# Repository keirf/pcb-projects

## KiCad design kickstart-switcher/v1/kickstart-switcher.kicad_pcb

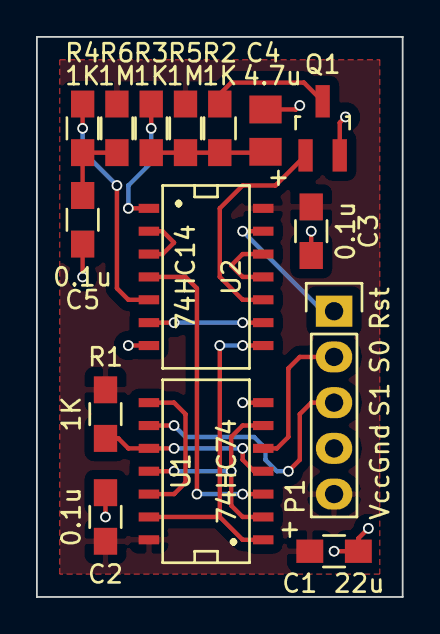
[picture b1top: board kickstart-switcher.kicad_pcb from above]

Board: 2 copper layers, 20.3 x 31.1 mm, 15 parts (0 on the bottom side), 19 nets.

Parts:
C1: 22u; R_0805_HandSoldering
C2, C3, C5: 0.1u; R_0805_HandSoldering
C4: 4.7u; TantalC_SizeR_EIA-2012
P1: CONN_01X05; Pin_Header_Straight_1x05
Q1: Q_NMOS; SOT-23_Handsoldering
R1, R2, R3, R4: 1K; R_0805_HandSoldering
R5, R6: 1M; R_0805_HandSoldering
U1: 74HC74; SOIC-14_N
U2: 74HC14; SOIC-14_N

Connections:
+5V: C1.1, C2.1, C3.1, P1.5, R1.1, R5.1, R6.1, U1.14, U2.14
//RESET: P1.1, U2.13
/CLR: U1.1, U1.13, U2.8
/SEL0: P1.2, U1.5
/SEL1: P1.3, U1.9
GND: C1.2, C2.2, C3.2, C4.2, C5.2, P1.4, Q1.2, U1.7, U2.7
unnamed: C4.1, R2.1, R3.2, R5.2
unnamed: C5.1, R4.2, R6.2
unnamed: Q1.1, U2.10
unnamed: Q1.3, R2.2
unnamed: R1.2, U1.4, U1.10
unnamed: R3.1, U2.1
unnamed: R4.1, U2.5
unnamed: U1.3, U2.4
unnamed: U1.2, U1.6, U1.11
unnamed: U1.8, U1.12
unnamed: U2.2, U2.3
unnamed: U2.6, U2.9
unnamed: U2.11, U2.12

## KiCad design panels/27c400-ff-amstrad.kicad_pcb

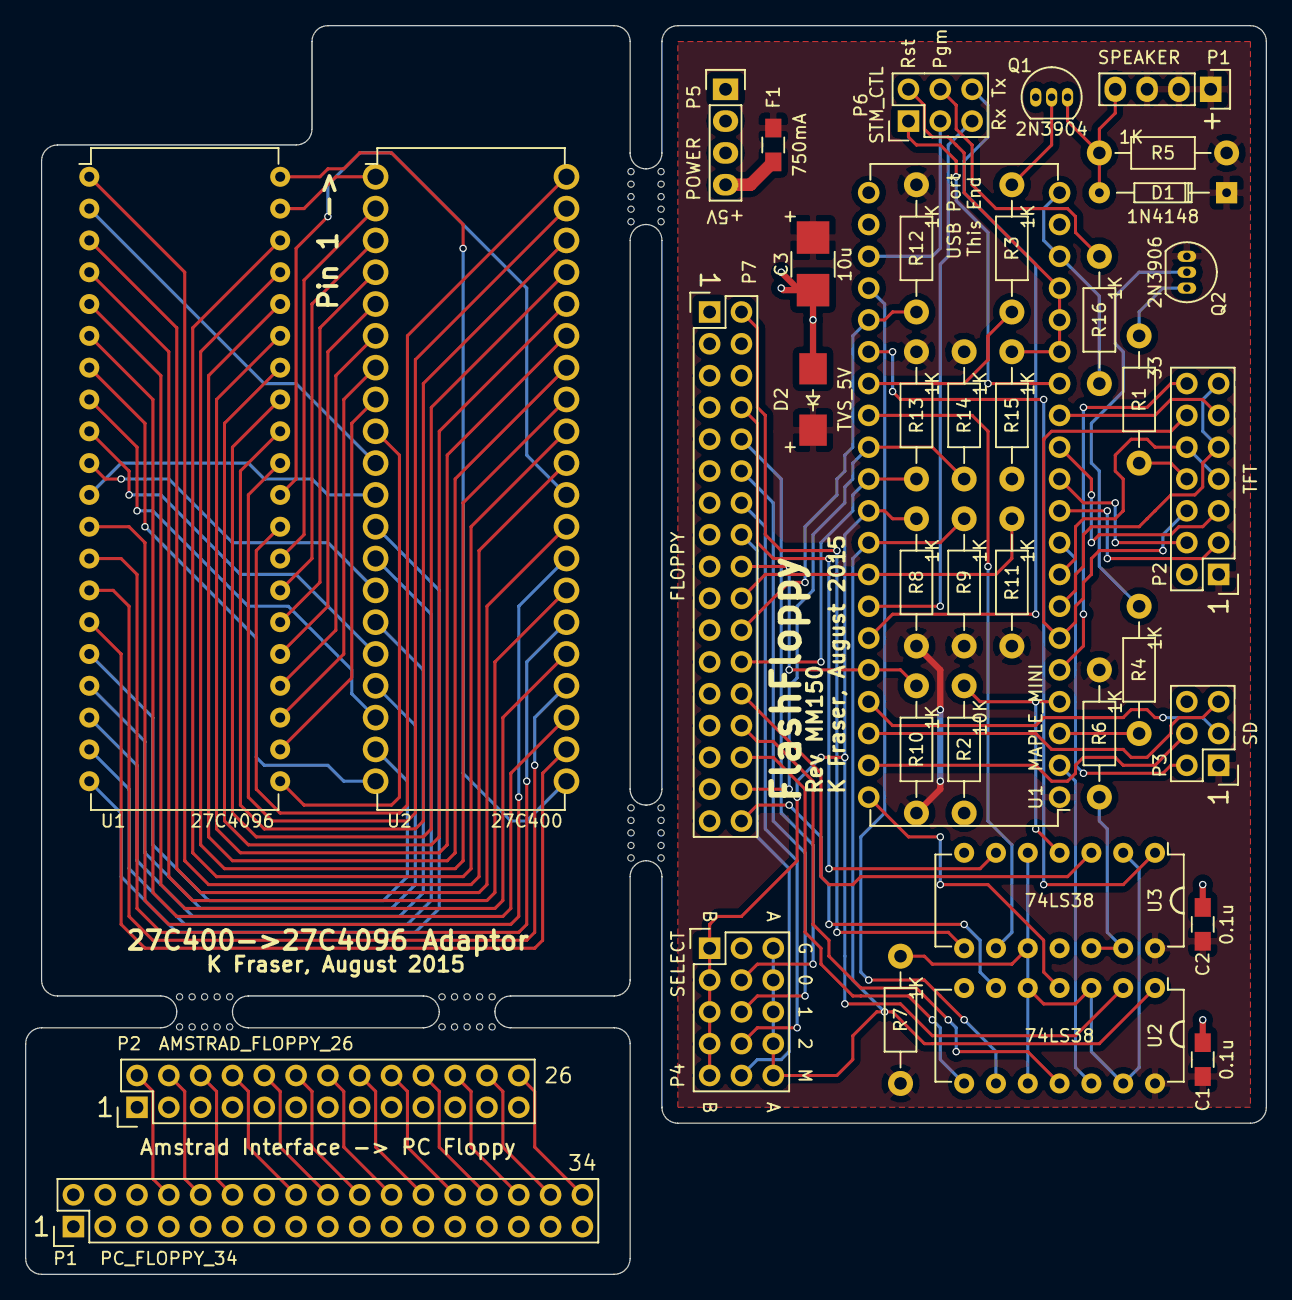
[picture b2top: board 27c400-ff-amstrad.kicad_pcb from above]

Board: 2 copper layers, 99.1 x 99.7 mm, 38 parts (0 on the bottom side), 105 nets.

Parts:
C1, C2: 0.1u; R_0805_HandSoldering
C3: 10u; C_3528
D1: 1N4148; Diode_DO-35_SOD27_Horizontal_RM10
D2: TVS_5V; D_SOD128
F1: 750mA; R_0805_HandSoldering
P1: SPEAKER; Pin_Header_Straight_1x04
P1#2: PC_FLOPPY_34; Pin_Header_Straight_2x17
P2: TFT; Pin_Header_Straight_2x07
P2#2: AMSTRAD_FLOPPY_26; Pin_Header_Straight_2x13
P3: SD; Pin_Header_Straight_2x03
P4: SELECT; Pin_Header_Straight_3x05
P5: POWER; Pin_Header_Straight_1x04
P6: STM_CTL; Pin_Header_Straight_2x03
P7: FLOPPY; Pin_Header_Straight_2x17
Q1: 2N3904; TO-92_Inline_Narrow_Oval
Q2: 2N3906; TO-92_Inline_Narrow_Oval
R1: 33; Resistor_Horizontal_RM10mm
R2: 10K; Resistor_Horizontal_RM10mm
R3, R4, R5, R6, R7, R8, R9, R10, R11, R12, R13, R14, R15, R16: 1K; Resistor_Horizontal_RM10mm
U1: 27C4096
U1#2: MAPLE_MINI; MMini-DIP-40
U2: 27C400
U2#2, U3: 74LS38; DIP-14_W7.62mm

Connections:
+5V: C1.1, C2.1, C3.1, D1.1, D2.1, F1.2, P1.1, P1.2, P1.3, P2.1, P3.1, Q2.1, R5.1, R6.1, R7.1, R8.1, R9.1, R10.1, R11.1, R12.1, R13.1, R14.1, U1#2.1, U2#2.14, U3.14
/3V3: R16.1, U1#2.18, U1#2.20
/BOOT0: P6.3, U1#2.23
/CHNG: U1#2.28, U3.9
/DIR: P1#2.18, P2#2.10
/DKRD: U1#2.24, U2#2.9
/GND: P1#2.1, P1#2.3, P1#2.5, P1#2.7, P1#2.9, P1#2.11, P1#2.13, P1#2.15, P1#2.17, P1#2.19, P1#2.21, P1#2.23, P1#2.25, P1#2.27, P1#2.29, P1#2.31, P1#2.33, P2#2.1, P2#2.3, P2#2.5, P2#2.7, P2#2.9, P2#2.11, P2#2.13, P2#2.15, P2#2.17, P2#2.19, P2#2.21, P2#2.23, P2#2.25
/IDX: P1#2.8, P2#2.2
/INDEX: R2.1, U1#2.4, U3.4
/LED_PWM: R4.1, U1#2.3
/MTR: P1#2.16, P2#2.8
/P1: U1.1, U2.31
/P2: U1.2, U2.10
/P3: U1.3, U2.29
/P4: U1.4, U2.27
/P5: U1.5, U2.25
/P6: U1.6, U2.23
/P7: U1.7, U2.20
/P8: U1.8, U2.18
/P9: U1.9, U2.16
/P10: U1.10, U2.14
/P11: U1.11, U2.11
/P12: U1.12, U2.28
/P13: U1.13, U2.26
/P14: U1.14, U2.24
/P15: U1.15, U2.22
/P16: U1.16, U2.19
/P17: U1.17, U2.17
/P18: U1.18, U2.15
/P19: U1.19, U2.13
/P20: U1.20, U2.12
/P21: U1.21, U2.9
/P22: U1.22, U2.8
/P23: U1.23, U2.7
/P24: U1.24, U2.6
/P25: U1.25, U2.5
/P26: U1.26, U2.4
/P27: U1.27, U2.3
/P28: U1.28, U2.2
/P29: U1.29, U2.40
/P30: U1.30, U2.30
/P31: U1.31, U2.39
/P32: U1.32, U2.38
/P33: U1.33, U2.37
/P34: U1.34, U2.36
/P35: U1.35, U2.35
/P36: U1.36, U2.34
/P37: U1.37, U2.33
/P38: U1.38, U2.32
/P39: U1.39, U2.1
/P40: U1.40, U2.21
/P_DN: P6.2, R15.2, U1#2.15, U1#2.16, U1#2.17
/P_UP: P6.4, R16.2
/RDATA: P1#2.30, P2#2.22
/RDY: P1#2.34, P2#2.26, U1#2.40, U2#2.4
/RESET: P6.1, U1#2.14
/SD_CK: P3.4, U1#2.39
/SD_CS: P3.2, U1#2.9
/SD_MISO: P3.5, U1#2.38
/SD_MOSI: P3.3, U1#2.37
/SEL: R7.2, U2#2.3, U2#2.5, U2#2.10, U2#2.13, U3.2, U3.5, U3.10
/SEL0: P1#2.10, P2#2.4
/SEL1: P1#2.12, P2#2.6
/SER_RX: P6.5, U1#2.34
/SER_TX: P6.6, U1#2.35
/SIDE: P1#2.32, P2#2.24
/SPK_PWM: R3.2, U1#2.27
/STEP: P1#2.20, P2#2.12
/TFT_CK: P2.7, P2.10, U1#2.8
/TFT_CS: P2.3, U1#2.10
/TFT_DCRS: P2.5, U1#2.12
/TFT_LED: P2.8, R1.2
/TFT_MISO: P2.9, P2.13, U1#2.7
/TFT_MOSI: P2.6, P2.12, U1#2.6
/TFT_RESET: P2.4, U1#2.11
/TRK0: P1#2.26, P2#2.18, U1#2.26, U3.1
/T_CS: P2.11, U1#2.13
/T_IRQ: P2.14, U1#2.5
/WDATA: P1#2.22, P2#2.14
/WGATE: P1#2.24, P2#2.16
/WRPROT: P1#2.28, P2#2.20, U1#2.2, U2#2.12
/_CHNG: P7.2, U3.8
/_DIR: P7.18, R10.2, U1#2.36
/_DKRD: P7.30, U2#2.8
/_DKWD: P7.22, R12.2, U1#2.25
/_DKWE: P7.24, R13.2, U1#2.30
/_INDEX: P7.8, U3.6
/_MTR: P4.10, P7.16
/_RDY: P7.34, U2#2.6
/_SEL0: P4.7, P7.10
/_SEL1: P4.8, P7.12
/_SEL2: P4.9, P7.14
/_SELA: P4.11, P4.12, P4.13, P4.14, P4.15, R9.2, U1#2.32, U2#2.1
/_SELB: P4.1, P4.2, P4.3, P4.4, P4.5, R8.2, U1#2.31, U2#2.2
/_SIDE: P7.32, R14.2, U1#2.29
/_STEP: P7.20, R11.2, U1#2.33
/_TRK0: P7.26, U3.3
/_WRPROT: P7.28, U2#2.11
GND: C1.2, C2.2, C3.2, D2.2, P2.2, P3.6, P4.6, P5.2, P5.3, P7.1, P7.3, P7.5, P7.7, P7.9, P7.11, P7.13, P7.15, P7.17, P7.19, P7.21, P7.23, P7.25, P7.27, P7.29, P7.31, P7.33, Q1.1, R2.2, R15.1, U1#2.19, U1#2.22, U2#2.7, U3.7
unnamed: D1.2, P1.4, Q1.3, R5.2
unnamed: F1.1, P5.4
unnamed: Q1.2, R3.1
unnamed: Q2.2, R4.2
unnamed: Q2.3, R1.1
unnamed: R6.2, U3.12, U3.13
